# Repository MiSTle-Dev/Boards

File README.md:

The MiSTle projects can be used with off-the-shelf components and
some breadboard setup.

To simplify this the MiSTeryNano project provides additional custom designed hardware boards.

These boards are typically to be produced through a service like [JLCPCB](https://jlcpcb.com/). You might
want to check the [instructions in our wiki](https://github.com/MiSTle-Dev/.github/wiki/JLCPCB-Order).

## Shields and carrier boards

Shields are carrier boards that carry one or more off-the-shelf development boards, connect them and provide them with additional peripherals like USB Hubs, MIDI ports, Joystick ports etc.

  - The [MiSTeryShield20k](misteryshield20k) is a base board for
  the Tang Nano 20k and the M0S Dock with a DB9 joystick connector and
  MIDI ports
  - [MiSTeryShield20k RPiPico](misteryshield20k_rpipico) is a board similar to the
  [MiSTeryShield20k](misteryshield20k) but using a Raspberry Pi Pico instead of the M0S Dock and with a USB hub already built-in
  - The [MiSTeryShield20k lite](misteryshield20k_lite) is also a base
  board for the Tang Nano 20k. It includes the RP2040 and a USB-A
  port and is a minimal all-in-one solution for the Tang Nano 20k.
  - The [Icepi carrier](icepi_carrier) is a base board for the [Icepi-Zero](https://github.com/cheyao/icepi-zero) adds the FPGA Companion as well as USB and Joystick ports

## Complete stand-alone solutions

The stand-alone boards don't require any further daughter boards to be plugged in. They come with all the necessary parts
including the Companion, the FPGA and a set of useful peripherals already integrated into one single board. These boards are
also meant to be used as a basis for further designs using a modified set of peripherals or meant to fit certain cases.

  - The [MiSTeryDev20k](misterydev20k) was the first complete all-in-one MiSTle board. It's based on the the GW2AR-LV18 FPGA
  (the same one as on the Tang Nano 20k) and is fully compatible with any core developed for the Tang nano 20k.
  - The [MiSTle GW3A-LV20 Dev](mistle_gw3a_20) is derived from the [MiSTeryDev20k](misterydev20k) and replaces the GW2AR-LV18 FPGA
  with the GW3A-LV20 which is slightly newer and has a little more capacity than the GW2AR-LV18.

## MCU PMOD's

Many FPGA boards provide so-called PMOD ports. These can be used to add the FPGA Companion MCU to those boards. The
MCU PMOD's provide a PMOD connector to common MCU developments boards and makes them compatible with typical FPGA PMOD ports.

FPGA boards providing PMOD ports include the Tang Primer 20K, Primer 25K, Mega 60k/138K NEO, Mega138kPro and Console 60k/138k

  - The [PMOD M0S](m0s_pmod) provides a PMOD port for the M0S Dock (BL616 µC)
  - The [PMOD PiPico](pipico_pmod) provides a PMOD port for Raspberry Pi Pico and (W)ifi
  - The [PMOD PiZero](pizero_pmod) provides a PMOD port for Raspberry Pi Pico compatible RP2040-ZERO board

## Other boards

  - The [Console Hub](console_hub) is a small 4 port USB Hub designed to be used with the Tang Console allowing it to be powered via USB-C through the Hub.
  - The [T20 PMOD](t20_pmod) is an add-on for the Efinix T20BGA256 development board adding a PMOD for HDMI usage, the SD card slot and a Raspberry Pi PICO incl. USB-A header to it making it a complete MiSTeryNano setup.
  - The [LVDS2TMDS board](lvds2tmds) is and add-on for the Efinix T20BGA256 development board converting its LVDS outputs to TMDS allowing to drive regular digital video signals
  - The [Atari ST Keyboard](atarist_keyboard) design is a tiny 50% Atari ST style keyboard which is meant to become the basis for a Mini Atari ST
  - [MisteryShield20k DS2 Adapter](misteryshield20k_ds2_adapter) is an add-on for the [MiSTeryShield20k](misteryshield20k) allowing to connect Playstation Dualshock 2 Game controllers to it

## Related projects

Further hardware is available in related projects:

  - [MisteryNano Case](https://github.com/prcoder-1/MiSTeryNano-Case) is a 3d printable case design for the bare Tang Nano 20k (no shields) with room and mounting instructions for expansion connectors and an optional M0S Dock
  - [Nano-Hub](https://github.com/Mangerrione/Nano-Hub), a Tang Nano 20k sized USB Hub
  - [Nano-Box](https://github.com/Mangerrione/Nano-Box), a Amiga themed case for the NanoMig

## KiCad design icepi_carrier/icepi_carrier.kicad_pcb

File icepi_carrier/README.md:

# MiSTle Icepi Carrier

This is a carrier/base board for the [Icepi-Zero](https://github.com/cheyao/icepi-zero).
It adds the FPGA Companion with its USB ports and two classic Dsub9 joystick ports.

The IcePi mounts face down onto the carrier which will then provide the IcePi with an
[RP2350 as FPGA Companion](https://github.com/MiSTle-Dev/FPGA-Companion), two DB9
joystick/mouse ports and a few LEDs.

> [!WARNING]
> The IcePi Zero needs to be mounted face down. Otherwise the IcePi and/or the carrier
> board may be damaged!

This carrier board is supported by the [Lattice/IcePi port of NanoMig](https://github.com/MiSTle-Dev/NanoMig/tree/main/src/lattice/icepi-zero). 

> [!IMPORTANT]
> The 3.3V voltage regulation of the IcePi is being used for the carrier as well. This means
> that the RP2350 on the carrier will not work without the IcePi installed.

The RP2350 on the IcePi Carrier runs the [PICO2 variant of the FPGA Companion firmware](https://github.com/MiSTle-Dev/FPGA-Companion/tree/main/src/rp2040) which is configured like so:

```
$ cd FPGA-Companion/src/rp2040
$ mkdir build
$ cd build
$ cmake -DBOARD=PICO2 ..
...
$ make
```

The resulting ```fpga_companion.uf2``` can be copied via USB to the Carrier.

See the [schematics](icepi_carrier_sch.pdf) and the [board layout](icepi_carrier_pcb.pdf).

## Production

This board can be manfactured through [JLCPCBs assembly service](http://jlcpcb.com) using the [production data](production). The production data does not include the pin header/socket required to mount the IcePi as this needs to match what's mounted on the IcePi itself.

## History

  - V1.0: Initial version
  - V1.0a: Replaced ws2812b with slightly bigger one with better availability at JLC

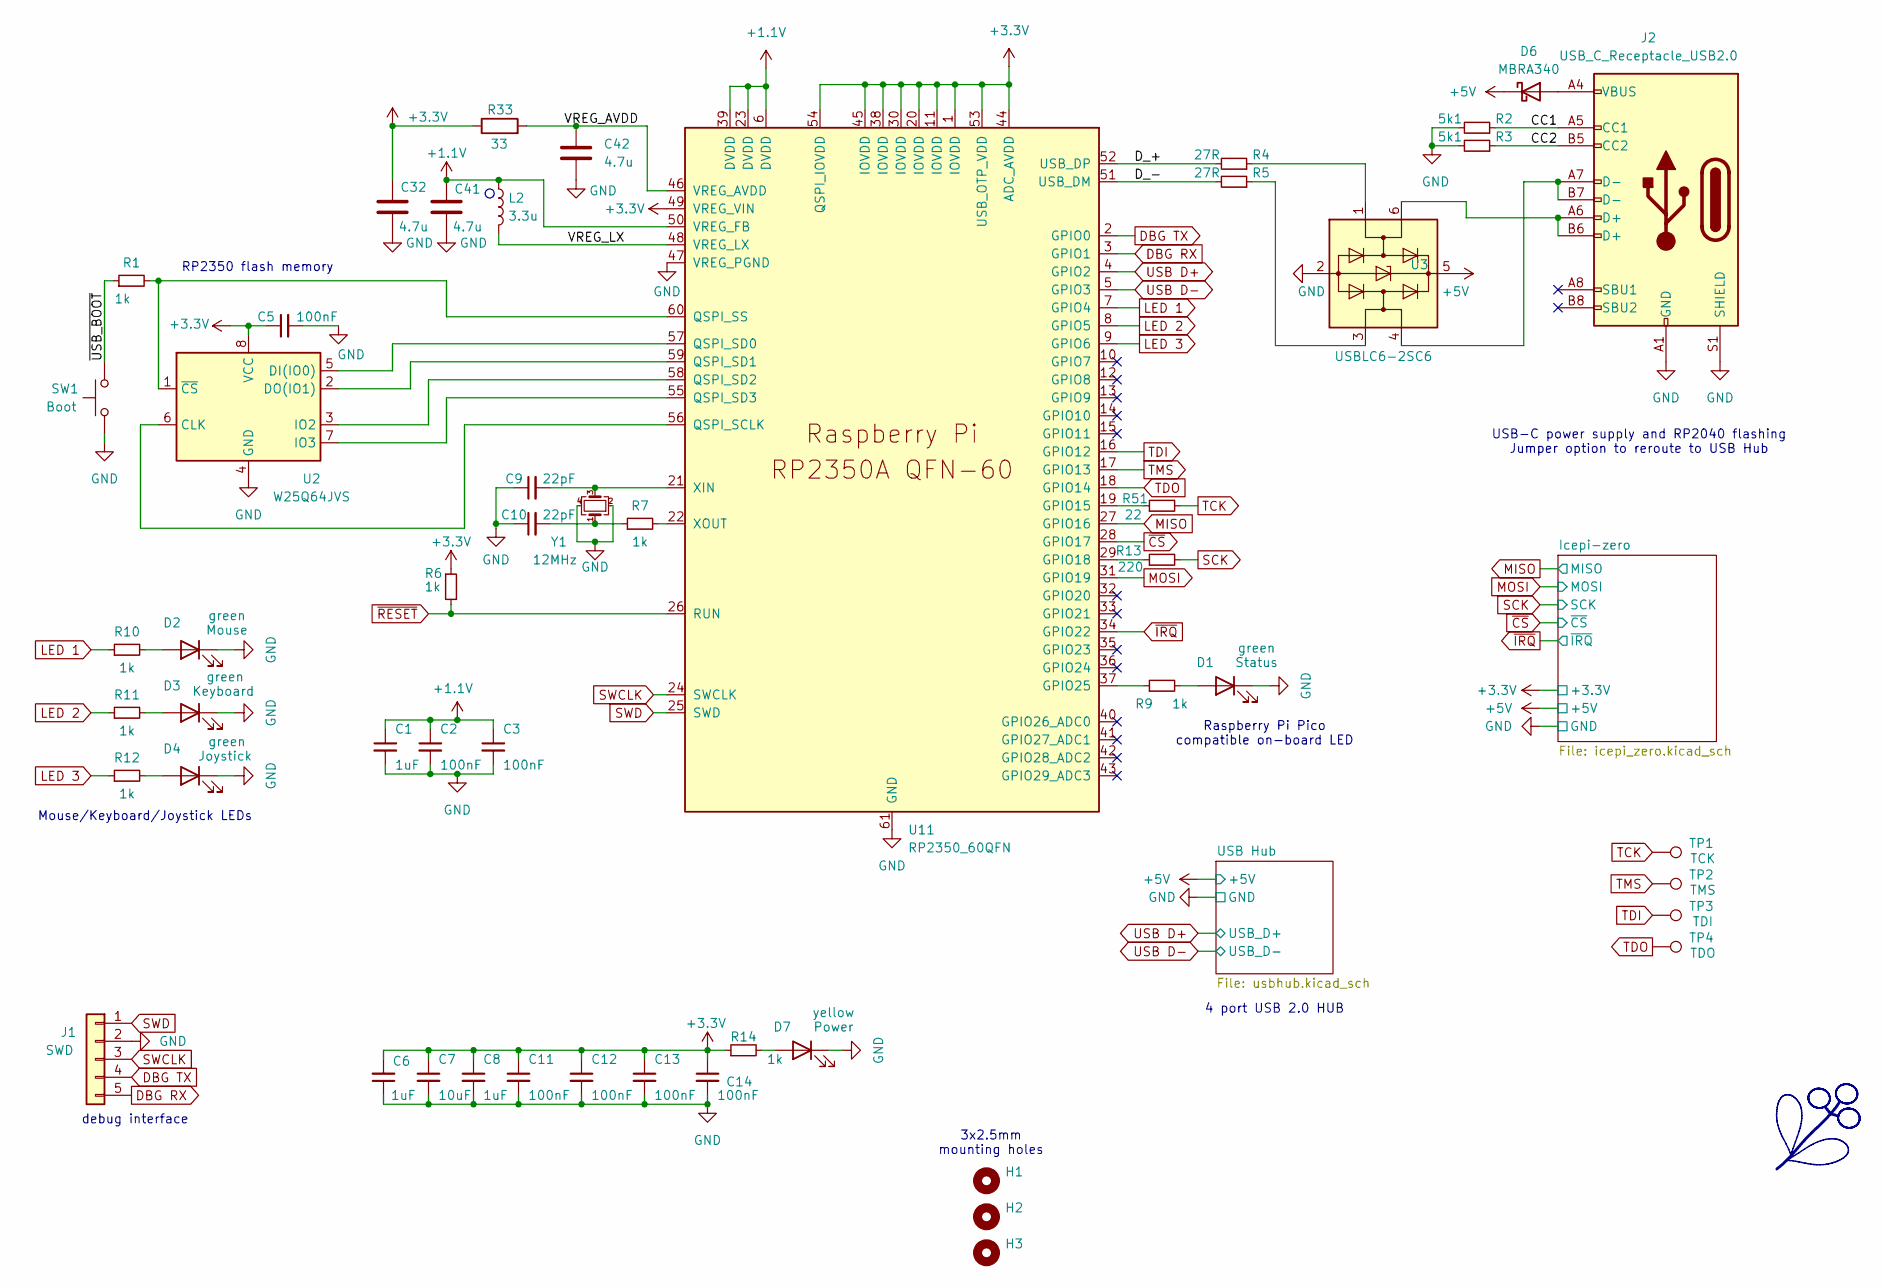
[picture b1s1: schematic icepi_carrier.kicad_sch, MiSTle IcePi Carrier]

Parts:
C1, C6, C8: 1uF; C_0402_1005Metric; LCSC Part # C52923
C2, C3, C5, C11, C12, C13, C14: 100nF; C_0402_1005Metric; LCSC Part # C1525
C7: 10uF; C_0402_1005Metric; LCSC Part # C15525
C9, C10: 22pF; C_0402_1005Metric; LCSC Part # C1555
C32, C41, C42: 4.7u; C_0402_1005Metric; LCSC Part # C23733
D1, D2, D3, D4: green; LED_0805_2012Metric; LCSC Part # C2297
D6: MBRA340; D_SMA; LCSC Part # C8678
D7: yellow; LED_0805_2012Metric; LCSC Part # C2296
H1, H2, H3: MountingHole; MountingHole_2.7mm_M2.5
J1: SWD; PinHeader_1x05_P2.54mm_Horizontal; LCSC Part # C492404
J2: USB_C_Receptacle_USB2.0; USB_C_Receptacle_HRO_TYPE-C-31-M-12; LCSC Part # C165948
L2: 3.3u; L_Changjiang_FTC201610D; LCSC Part # C42411119
R1, R6, R7, R9, R10, R11, R12, R14: 1k; R_0402_1005Metric; LCSC Part # C11702
R2, R3: 5k1; R_0402_1005Metric; LCSC Part # C25905
R4, R5: 27R; R_0603_1608Metric; LCSC Part # C25190
R13: 220; R_0402_1005Metric; LCSC Part # C25091
R33: 33; R_0402_1005Metric; LCSC Part # C25105
R51: 22; R_0402_1005Metric; LCSC Part # C25092
SW1: Boot; SW_SPST_TL3342; LCSC Part # C318884
TP1, TP2, TP3, TP4: TestPoint; TestPoint_Pad_D1.0mm
U2: W25Q64JVS; SOIC-8_5.3x5.3mm_P1.27mm; LCSC Part # C179171
U3: USBLC6-2SC6; SOT-23-6; LCSC Part # C2827654
U11: RP2350_60QFN; RP2350-QFN-60-1EP_7x7_P0.4mm_EP3.4x3.4mm_ThermalVias; LCSC Part # C42411118
Y1: 12MHz; Crystal_SMD_3225-4Pin_3.2x2.5mm; LCSC Part # C20625731

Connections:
+1.1V: C1.1, C2.1, C3.1, C41.1, L2.1, U11.6 (DVDD), U11.23 (DVDD), U11.39 (DVDD), U11.50 (VREG_FB)
+3.3V: C5.1, C6.2, C7.1, C8.1, C11.1, C12.1, C13.1, C14.1, C32.1, R6.1, R14.1, R33.1, U2.8 (VCC), U11.1 (IOVDD), U11.11 (IOVDD), U11.20 (IOVDD), U11.30 (IOVDD), U11.38 (IOVDD), U11.44 (ADC_AVDD), U11.45 (IOVDD), U11.49 (VREG_VIN), U11.53 (USB_OTP_VDD), U11.54 (QSPI_IOVDD); also elsewhere on the board
+5V: D6.1 (K), U3.5 (VBUS); also elsewhere on the board
/CC1: J2.A5 (CC1), R2.1
/CC2: J2.B5 (CC2), R3.1
/D_+: R4.2, U11.52 (USB_DP)
/D_-: R5.2, U11.51 (USB_DM)
/VREG_AVDD: C42.1, R33.2, U11.46 (VREG_AVDD)
/VREG_LX: L2.2, U11.48 (VREG_LX)
/~USB_BOOT: R1.1, SW1.2
DBG RX: J1.5, U11.3 (GPIO1)
DBG TX: J1.4, U11.2 (GPIO0)
GND: C1.2, C2.2, C3.2, C5.2, C6.1, C7.2, C8.2, C9.1, C10.1, C11.2, C12.2, C13.2, C14.2, C32.2, C41.2, C42.2, D1.1 (K), D2.1 (K), D3.1 (K), D4.1 (K), D7.1 (K), J1.2, J2.A1 (GND), J2.A12 (GND), J2.B1 (GND), J2.B12 (GND), J2.S1 (SHIELD), R2.2, R3.2, SW1.1, U2.4 (GND), U3.2 (GND), U11.47 (VREG_PGND), U11.61 (GND), Y1.2, Y1.4; also elsewhere on the board
LED 1: R10.1, U11.7 (GPIO4)
LED 2: R11.1, U11.8 (GPIO5)
LED 3: R12.1, U11.9 (GPIO6)
MISO: U11.27 (GPIO16); also elsewhere on the board
MOSI: U11.31 (GPIO19); also elsewhere on the board
unnamed: C10.2, R7.1, Y1.1
unnamed: D1.2 (A), R9.2
unnamed: D2.2 (A), R10.2
unnamed: D3.2 (A), R11.2
unnamed: D4.2 (A), R12.2
unnamed: D6.2 (A), J2.A4 (VBUS), J2.A9 (VBUS), J2.B4 (VBUS), J2.B9 (VBUS)
unnamed: D7.2 (A), R14.2
unnamed: J2.A6 (D+), J2.B6 (D+), U3.6 (I/O1)
unnamed: J2.A7 (D-), J2.B7 (D-), U3.4 (I/O2)
unnamed: R4.1, U3.1 (I/O1)
unnamed: R5.1, U3.3 (I/O2)
unnamed: R51.1, U11.19 (GPIO15)
unnamed: R13.1, U11.29 (GPIO18)
unnamed: R9.1, U11.37 (GPIO25)
unnamed: U2.6 (CLK), U11.56 (QSPI_SCLK)
unnamed: U2.5 (DI(IO0)), U11.57 (QSPI_SD0)
unnamed: U2.2 (DO(IO1)), U11.59 (QSPI_SD1)
unnamed: U2.3 (IO2), U11.58 (QSPI_SD2)
unnamed: U2.7 (IO3), U11.55 (QSPI_SD3)
unnamed: R1.2, U2.1 (~CS), U11.60 (QSPI_SS)
unnamed: C9.2, U11.21 (XIN), Y1.3
unnamed: R7.2, U11.22 (XOUT)
SCK: R13.2; also elsewhere on the board
SWCLK: J1.3, U11.24 (SWCLK)
SWD: J1.1, U11.25 (SWD)
TCK: R51.2, TP1.1 (1_1)
TDI: TP3.1 (1_1), U11.16 (GPIO12)
TDO: TP4.1 (1_1), U11.18 (GPIO14)
TMS: TP2.1 (1_1), U11.17 (GPIO13)
USB D+: U11.4 (GPIO2); also elsewhere on the board
USB D-: U11.5 (GPIO3); also elsewhere on the board
~CS: U11.28 (GPIO17); also elsewhere on the board
~IRQ: U11.34 (GPIO22); also elsewhere on the board
~RESET: R6.2, U11.26 (RUN)

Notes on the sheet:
Mouse/Keyboard/Joystick LEDs
RP2350 flash memory
3x2.5mm mounting holes
4 port USB 2.0 HUB
debug interface
Raspberry Pi Pico compatible on-board LED
USB-C power supply and RP2040 flashing Jumper option to reroute to USB Hub

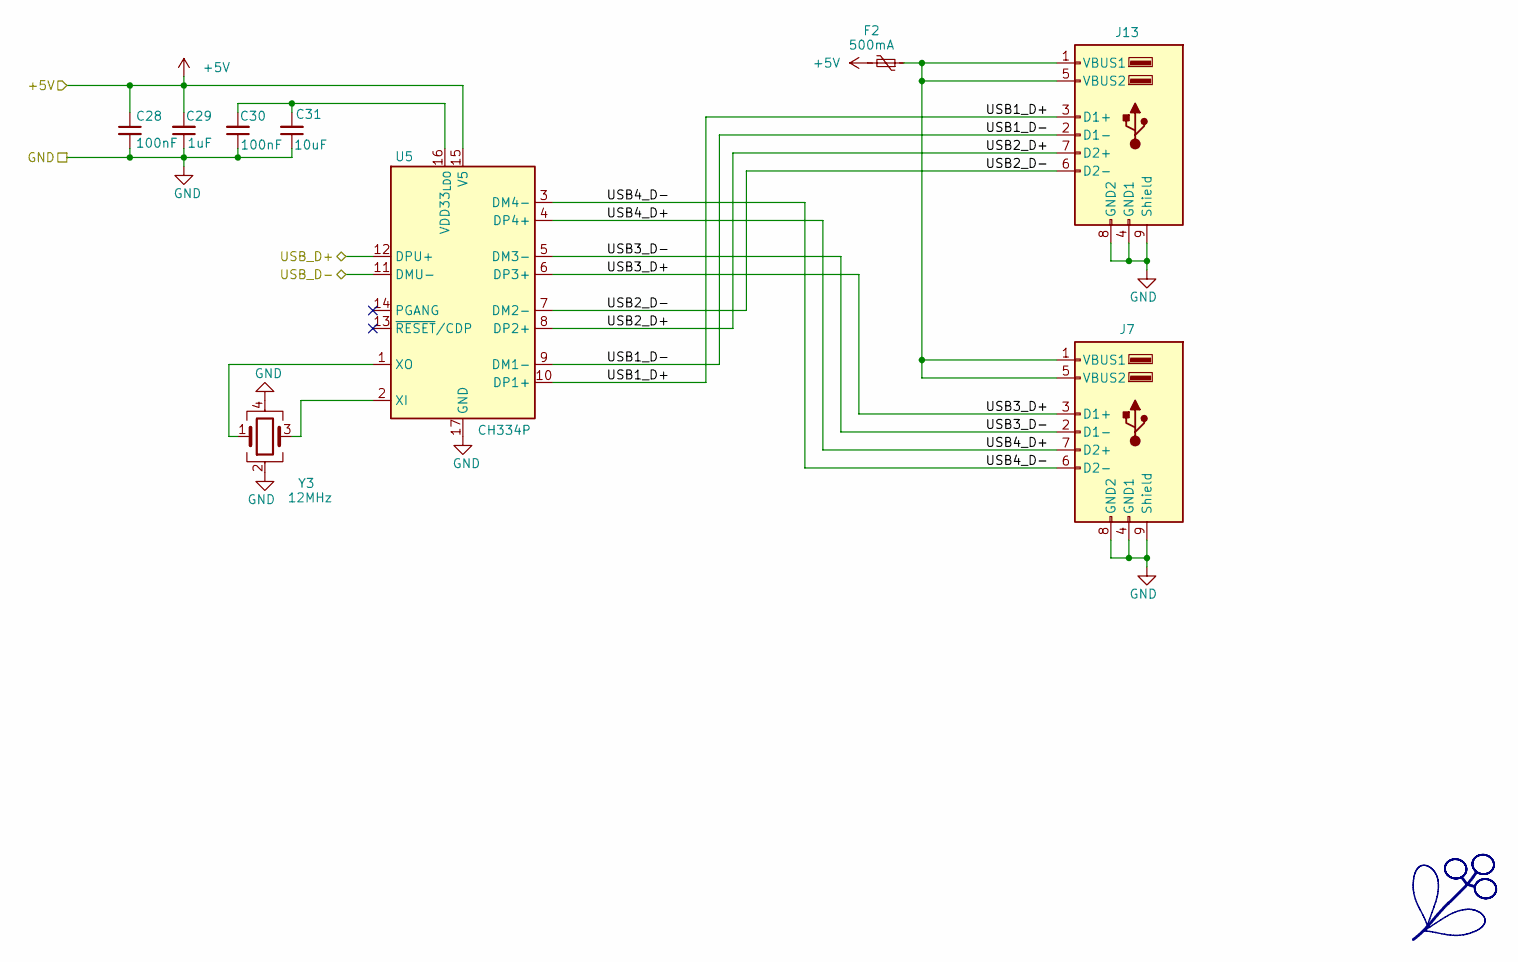
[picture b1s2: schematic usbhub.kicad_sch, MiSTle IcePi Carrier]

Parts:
C28, C30: 100nF; C_0402_1005Metric; LCSC Part # C1525
C29: 1uF; C_0402_1005Metric; LCSC Part # C52923
C31: 10uF; C_0402_1005Metric; LCSC Part # C15525
F2: 500mA; Fuse_1206_3216Metric; LCSC Part # C70076
J7, J13: USB_A_Stacked; USB_A_Wuerth_61400826021_Horizontal_Stacked; LCSC Part # C456021
U5: CH334P; QFN-16-1EP_3x3mm_P0.5mm_EP1.45x1.45mm_ThermalVias; LCSC Part # C5373042
Y3: 12MHz; Crystal_SMD_3225-4Pin_3.2x2.5mm; LCSC Part # C9002

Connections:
+5V: C28.1, C29.2, F2.2, U5.15 (V5); also elsewhere on the board
/USB Hub/USB1_D+: J13.3 (D1+), U5.10 (DP1+)
/USB Hub/USB1_D-: J13.2 (D1-), U5.9 (DM1-)
/USB Hub/USB2_D+: J13.7 (D2+), U5.8 (DP2+)
/USB Hub/USB2_D-: J13.6 (D2-), U5.7 (DM2-)
/USB Hub/USB3_D+: J7.3 (D1+), U5.6 (DP3+)
/USB Hub/USB3_D-: J7.2 (D1-), U5.5 (DM3-)
/USB Hub/USB4_D+: J7.7 (D2+), U5.4 (DP4+)
/USB Hub/USB4_D-: J7.6 (D2-), U5.3 (DM4-)
GND: C28.2, C29.1, C30.1, C31.1, J7.4 (GND1), J7.8 (GND2), J7.9 (Shield), J13.4 (GND1), J13.8 (GND2), J13.9 (Shield), U5.17 (GND), Y3.2, Y3.4; also elsewhere on the board
unnamed: F2.1, J7.1 (VBUS1), J7.5 (VBUS2), J13.1 (VBUS1), J13.5 (VBUS2)
unnamed: C30.2, C31.2, U5.16 (VDD33_{LDO})
unnamed: U5.2 (XI), Y3.3
unnamed: U5.1 (XO), Y3.1
USB D+: U5.12 (DPU+); also elsewhere on the board
USB D-: U5.11 (DMU-); also elsewhere on the board

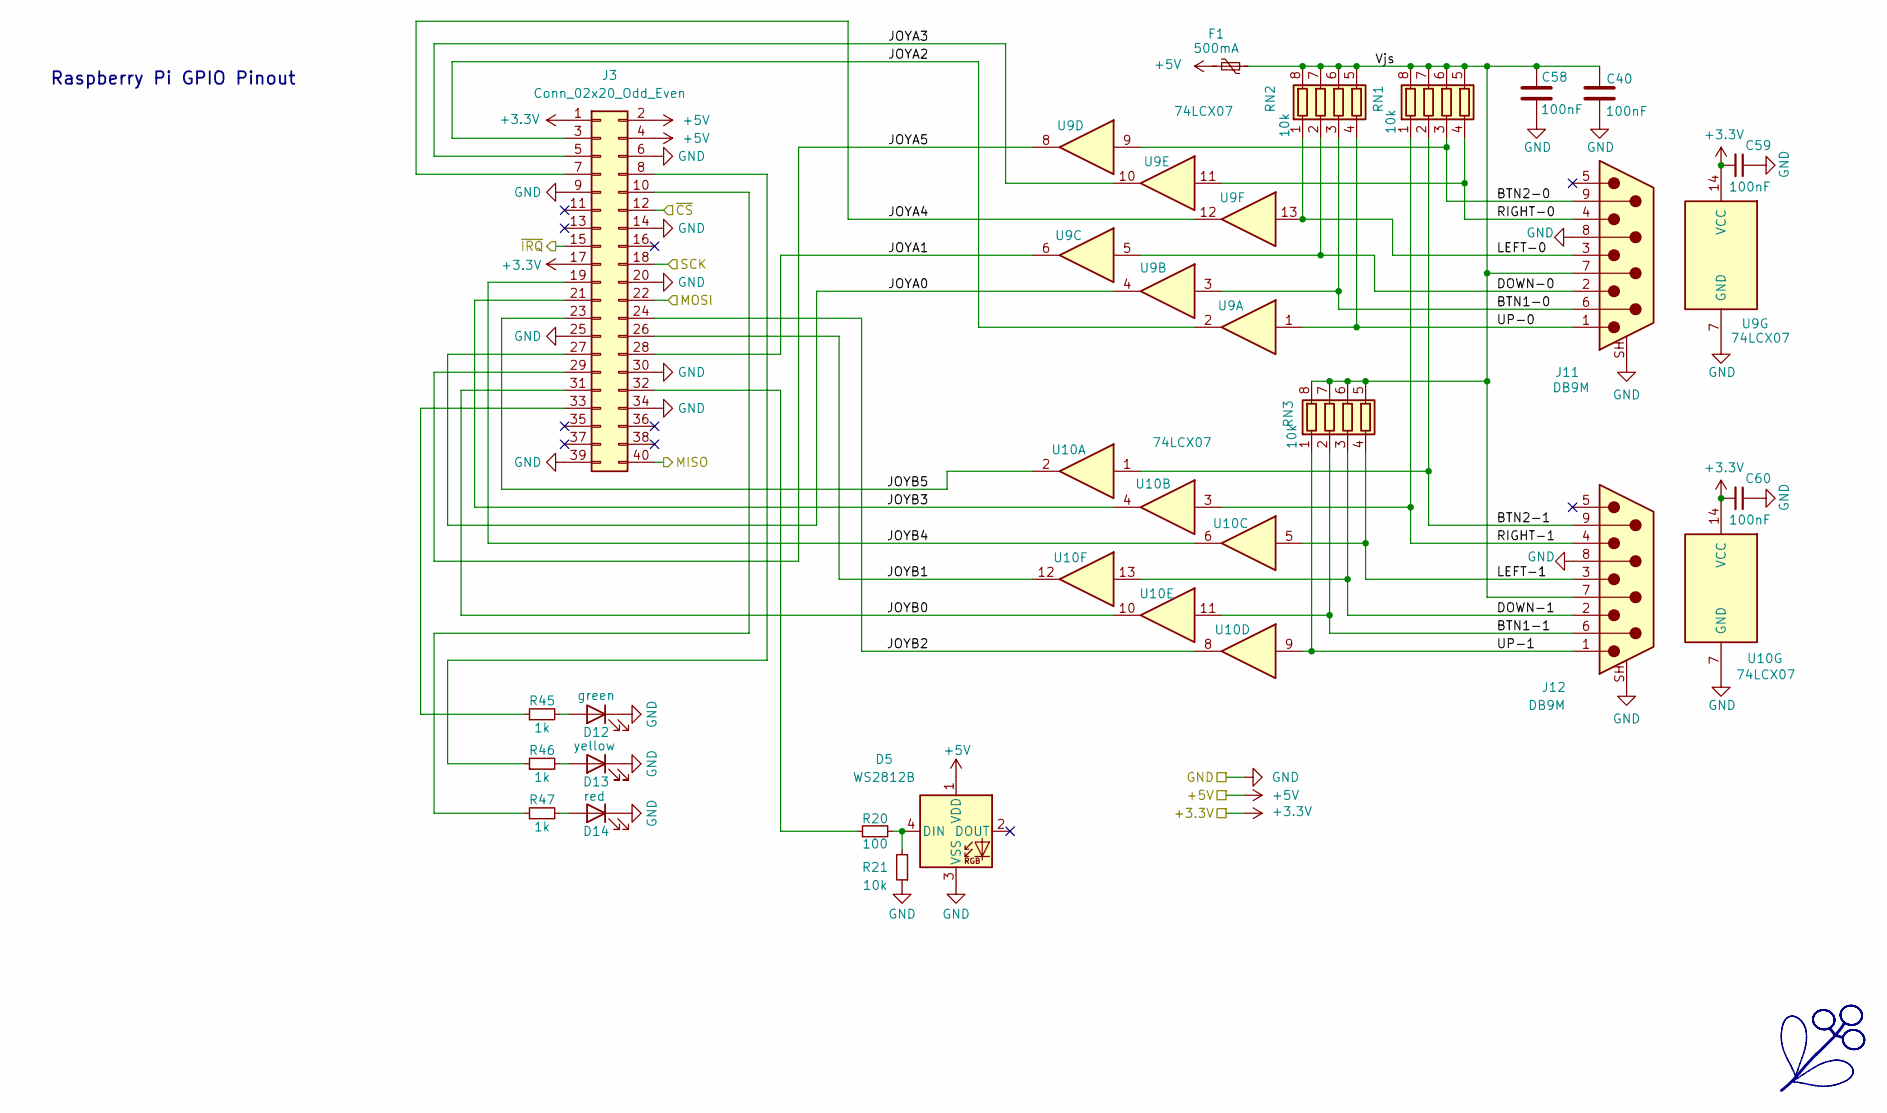
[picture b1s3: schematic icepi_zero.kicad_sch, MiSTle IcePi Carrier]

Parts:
C40, C58, C59, C60: 100nF; C_0402_1005Metric; LCSC Part # C1525
D5: WS2812B; LED_WS2812B-Mini_PLCC4_3.5x3.5mm; LCSC Part # C527089
D12: green; LED_0805_2012Metric; LCSC Part # C2297
D13: yellow; LED_0805_2012Metric; LCSC Part # C2296
D14: red; LED_0805_2012Metric; LCSC Part # C2295
F1: 500mA; Fuse_1206_3216Metric; LCSC Part # C70076
J3: Conn_02x20_Odd_Even; PinSocket_2x20_P2.54mm_Vertical
J11, J12: DB9M; DSUB-9_Pins_Horizontal_P2.77x2.84mm_EdgePinOffset7.70mm_Hou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; LCSC Part # C141880
R20: 100; R_0402_1005Metric; LCSC Part # C25076
R21: 10k; R_0402_1005Metric; LCSC Part # C25744
R45, R46, R47: 1k; R_0402_1005Metric; LCSC Part # C11702
RN1, RN2, RN3: 10k; R_Array_Concave_4x0603; LCSC Part # C110924
U9, U10: 74LCX07; TSSOP-14_4.4x5mm_P0.65mm; LCSC Part # C2676034

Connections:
+3.3V: C59.2, C60.2, J3.1, J3.17, U9.14 (VCC), U10.14 (VCC); also elsewhere on the board
+5V: D5.1 (VDD), F1.2, J3.2, J3.4; also elsewhere on the board
/Icepi-zero/BTN1-0: J11.6, RN2.3 (R3.1), U9.3
/Icepi-zero/BTN1-1: J12.6, RN3.2 (R2.1), U10.11
/Icepi-zero/BTN2-0: J11.9, RN1.3 (R3.1), U9.9
/Icepi-zero/BTN2-1: J12.9, RN1.2 (R2.1), U10.1
/Icepi-zero/DOWN-0: J11.2, RN2.2 (R2.1), U9.5
/Icepi-zero/DOWN-1: J12.2, RN3.3 (R3.1), U10.13
/Icepi-zero/JOYA0: J3.27, U9.4
/Icepi-zero/JOYA1: J3.28, U9.6
/Icepi-zero/JOYA2: J3.3, U9.2
/Icepi-zero/JOYA3: J3.5, U9.10
/Icepi-zero/JOYA4: J3.7, U9.12
/Icepi-zero/JOYA5: J3.29, U9.8
/Icepi-zero/JOYB0: J3.31, U10.10
/Icepi-zero/JOYB1: J3.26, U10.12
/Icepi-zero/JOYB2: J3.24, U10.8
/Icepi-zero/JOYB3: J3.21, U10.4
/Icepi-zero/JOYB4: J3.19, U10.6
/Icepi-zero/JOYB5: J3.23, U10.2
/Icepi-zero/LEFT-0: J11.3, RN2.1 (R1.1), U9.13
/Icepi-zero/LEFT-1: J12.3, RN3.4 (R4.1), U10.5
/Icepi-zero/RIGHT-0: J11.4, RN1.4 (R4.1), U9.11
/Icepi-zero/RIGHT-1: J12.4, RN1.1 (R1.1), U10.3
/Icepi-zero/UP-0: J11.1, RN2.4 (R4.1), U9.1
/Icepi-zero/UP-1: J12.1, RN3.1 (R1.1), U10.9
/Icepi-zero/Vjs: C40.2, C58.2, F1.1, J11.7, J12.7, RN1.5 (R4.2), RN1.6 (R3.2), RN1.7 (R2.2), RN1.8 (R1.2), RN2.5 (R4.2), RN2.6 (R3.2), RN2.7 (R2.2), RN2.8 (R1.2), RN3.5 (R4.2), RN3.6 (R3.2), RN3.7 (R2.2), RN3.8 (R1.2)
GND: C40.1, C58.1, C59.1, C60.1, D5.3 (VSS), D12.1 (K), D13.1 (K), D14.1 (K), J3.6, J3.9, J3.14, J3.20, J3.25, J3.30, J3.34, J3.39, J11.8, J11.SH (PAD), J12.8, J12.SH (PAD), R21.1, U9.7 (GND), U10.7 (GND); also elsewhere on the board
MISO: J3.40; also elsewhere on the board
MOSI: J3.22; also elsewhere on the board
unnamed: D5.4 (DIN), R20.2, R21.2
unnamed: D12.2 (A), R45.2
unnamed: D13.2 (A), R46.2
unnamed: D14.2 (A), R47.2
unnamed: J3.8, R46.1
unnamed: J3.10, R47.1
unnamed: J3.32, R20.1
unnamed: J3.33, R45.1
SCK: J3.18; also elsewhere on the board
~CS: J3.12; also elsewhere on the board
~IRQ: J3.15; also elsewhere on the board

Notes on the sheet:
Raspberry Pi GPIO Pinout

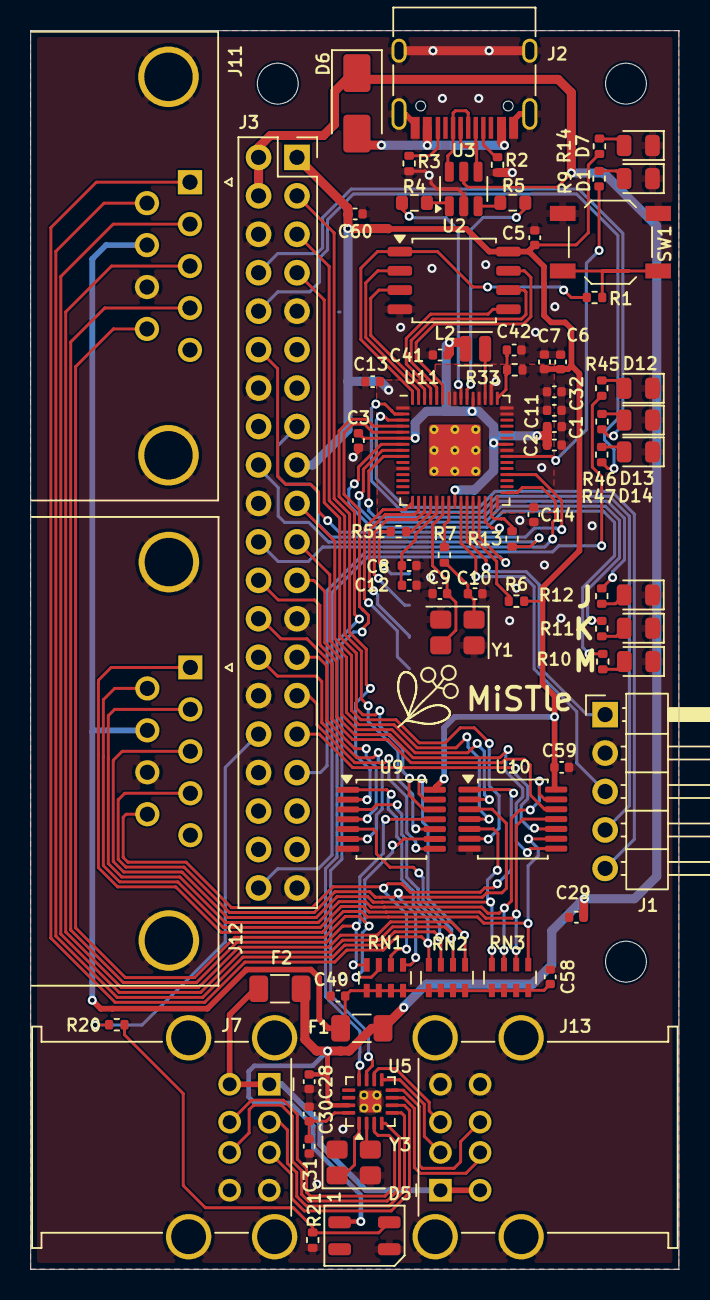
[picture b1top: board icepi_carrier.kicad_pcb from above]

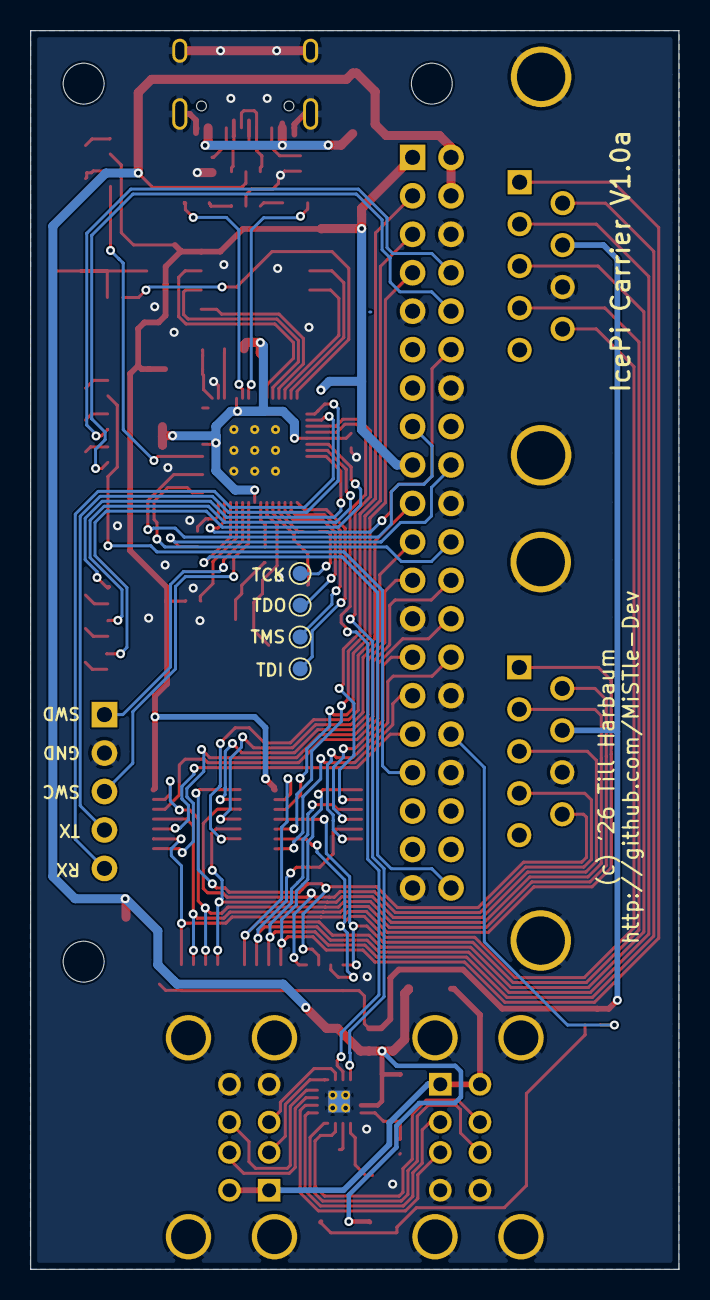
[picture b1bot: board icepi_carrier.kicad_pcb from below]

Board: 2 copper layers, 42.8 x 81.8 mm, 83 parts (4 on the bottom side), 97 nets.

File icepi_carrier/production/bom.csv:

Designator,Footprint,Quantity,Value,LCSC Part #
"C1, C29, C6, C8",0402,4,1uF,C52923
"C10, C9",0402,2,22pF,C1555
"C11, C12, C13, C14, C2, C28, C3, C30, C40, C5, C58, C59, C60",0402,13,100nF,C1525
"C31, C7",0402,2,10uF,C15525
"C32, C41, C42",0402,3,4.7u,C23733
"D1, D12, D2, D3, D4",0805,5,green,C2297
"D13, D7",0805,2,yellow,C2296
D14,0805,1,red,C2295
D5,LED_WS2812B-Mini_PLCC4_3.5x3.5mm,1,WS2812B,C527089
D6,D_SMA,1,MBRA340,C8678
"F1, F2",1206,2,500mA,C70076
J1,PinHeader_1x05_P2.54mm_Horizontal,1,SWD,C492404
"J11, J12",DSUB-9_Pins_Horizontal_P2.77x2.84mm_EdgePinOffset7.70mm_Housed_MountingHolesOffset9.12mm,2,DB9M,C141880
"J13, J7",USB_A_Wuerth_61400826021_Horizontal_Stacked,2,USB_A_Stacked,C456021
J2,USB_C_Receptacle_HRO_TYPE-C-31-M-12,1,USB_C_Receptacle_USB2.0,C165948
L2,L_Changjiang_FTC201610D,1,3.3u,C42411119
"R1, R10, R11, R12, R14, R45, R46, R47, R6, R7, R9",0402,11,1k,C11702
R13,0402,1,220,C25091
"R2, R3",0402,2,5k1,C25905
R20,0402,1,100,C25076
R21,0402,1,10k,C25744
R33,0402,1,33,C25105
"R4, R5",0603,2,27R,C25190
R51,0402,1,22,C25092
"RN1, RN2, RN3",R_Array_Concave_4x0603,3,10k,C110924
SW1,SW_SPST_TL3342,1,Boot,C318884
"U10, U9",TSSOP-14_4.4x5mm_P0.65mm,2,74LCX07,C2676034
U11,RP2350-QFN-60-1EP_7x7_P0.4mm_EP3.4x3.4mm_ThermalVias,1,RP2350_60QFN,C42411118
U2,SOIC-8_5.3x5.3mm_P1.27mm,1,W25Q64JVS,C179171
U3,SOT-23-6,1,USBLC6-2SC6,C2827654
U5,QFN-16-1EP_3x3mm_P0.5mm_EP1.45x1.45mm_ThermalVias,1,CH334P,C5373042
Y1,Crystal_SMD_3225-4Pin_3.2x2.5mm,1,12MHz,C20625731
Y3,Crystal_SMD_3225-4Pin_3.2x2.5mm,1,12MHz,C9002

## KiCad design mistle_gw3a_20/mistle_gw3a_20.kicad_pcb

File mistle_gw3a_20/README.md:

# GW3A-LV20/GW5A-LV25 DEV25K MiSTle development board

This board is derived from the [MiSTeryDev20k
board](https://github.com/MiSTle-Dev/Boards/tree/main/misterydev20k)
which was the first full custom board designed for the MiSTle project.

This board is a development board initially designed to test the
upcoming [GW3A-LV20 FPGA](https://www.gowinsemi.com/en/product/detail/84/) with the MiSTle
retro computing cores. It can also be used with the existing GW5A-LV25
FPGA as seen in the image above.

The NanoMig and C64Nano had [been
prepared to run on the GW3A](https://github.com/MiSTle-Dev/NanoMig/tree/main/src/mistle/gw3a_20)
to ensure that the cores can be synthesized and especially to verify
the pin mapping. Depiced above is the board with the GW5A-25K mounted and running
the [GW5A-LV25 variant](https://github.com/MiSTle-Dev/NanoMig/tree/main/src/mistle/gw5a_25)
of the [NanoMig FPGA Core](https://github.com/MiSTle-Dev/NanoMig).

## Goals
  - Get used to the new GW3A family of FPGAs
    - Update openFPGAloader
    - Verify use of external SDRAM
  - Update Companion to RP2350
    - Use additional PIO for JTAG

## Current state

  - Initial schematic and board derived from the [MiSTeryDev20k board](https://github.com/MiSTle-Dev/Boards/tree/main/misterydev20k)
  - [NanoMig](https://github.com/MiSTle-Dev/NanoMig) core [synthesized for GW3A-LV20](https://github.com/MiSTle-Dev/NanoMig/tree/main/src/mistle/gw3a_20) :heavy_check_mark:
    - LUT usage around 80%
  - Schematic updates
    - GW2AR-LV18 FPGA replaced by GW3A-LV20 :heavy_check_mark:
    - Updated pin mapping :heavy_check_mark:
    - Added external 256MBit (16M*16) SDRAM as the GW3A-LV20 has no internal SDRAM :heavy_check_mark: 
    - External peripherals mapped :heavy_check_mark:
    - Update FPGA Power Supply :heavy_check_mark:
    - Add smoothing capacitors and similar :heavy_check_mark:
    - Initial routing :heavy_check_mark:
    - Verify schematic :wrench:
       - Check updated SD card wiring :heavy_check_mark:
       - Check FPGA power supply :heavy_check_mark:
       - Update from rp2040 to rp2350 :heavy_check_mark:
       - Check compatibility with GW5A-LV25-LQ144 :heavy_check_mark:
    - Verify PCB :wrench:
    - Update JLCPCB part numbers :heavy_check_mark:
    - Generate [JLCPCB production data](production) :heavy_check_mark:
    - Order partially assembled boards :heavy_check_mark:
    - Order FPGAs :heavy_check_mark:	
    - Waiting for delivery :heavy_check_mark:	
    - Update Companion firmware for rp2350 :heavy_check_mark:	
    - Solder and test FPGA :heavy_check_mark:	
    - Solder and test SDRAM :heavy_check_mark:
    - Testing :heavy_check_mark:
    - Make use of bigger FPGA (AGA)

## FPGA Companion

The FPGA Companion needs to be built with

   ```cmake -DBOARD=DEV25K ..```

The Companion will then act as the regular support device during
runtime but will also provide USB/JTAG functionality for setup and
flashing from a PC.

## Cores

Currently the NanoMig and C64Nano had been ported to this board. A tested and
fully working core for the GW5A-25K is available and can be built using
the following command:

   ```build.sh mistle_gw5a_25```

The GW3A-20K NanoMig variant can also be built in similar way:

   ```build.sh mistle_gw3a_20```

This is untested for obvious reasons.

## Issues with V1.0

  - Polarity of ```MODE0``` os wrong and prevents FPGA flash boot/usage
  - Flash ```IO2``` and ```IO3``` should probably be FPGA pins ```MI2``` and ```MI3``` instead ```DO2``` and ```DO3```. This is not critical but probably prevents a QSPI FPGA boot. This is misleading in figure 4-4 of [UG1356-1.0E_GW3A series of FPGA Products Schematic Manual.pdf](https://www.gowinsemi.com/en/document/chkLogin/?forward=product%2C3373).

## Preliminary schematic

The schematic is a work in progress and can be viewed [here](https://github.com/MiSTle-Dev/Boards/blob/main/mistle_gw3a_20/mistle_gw3a_20_sch.pdf).

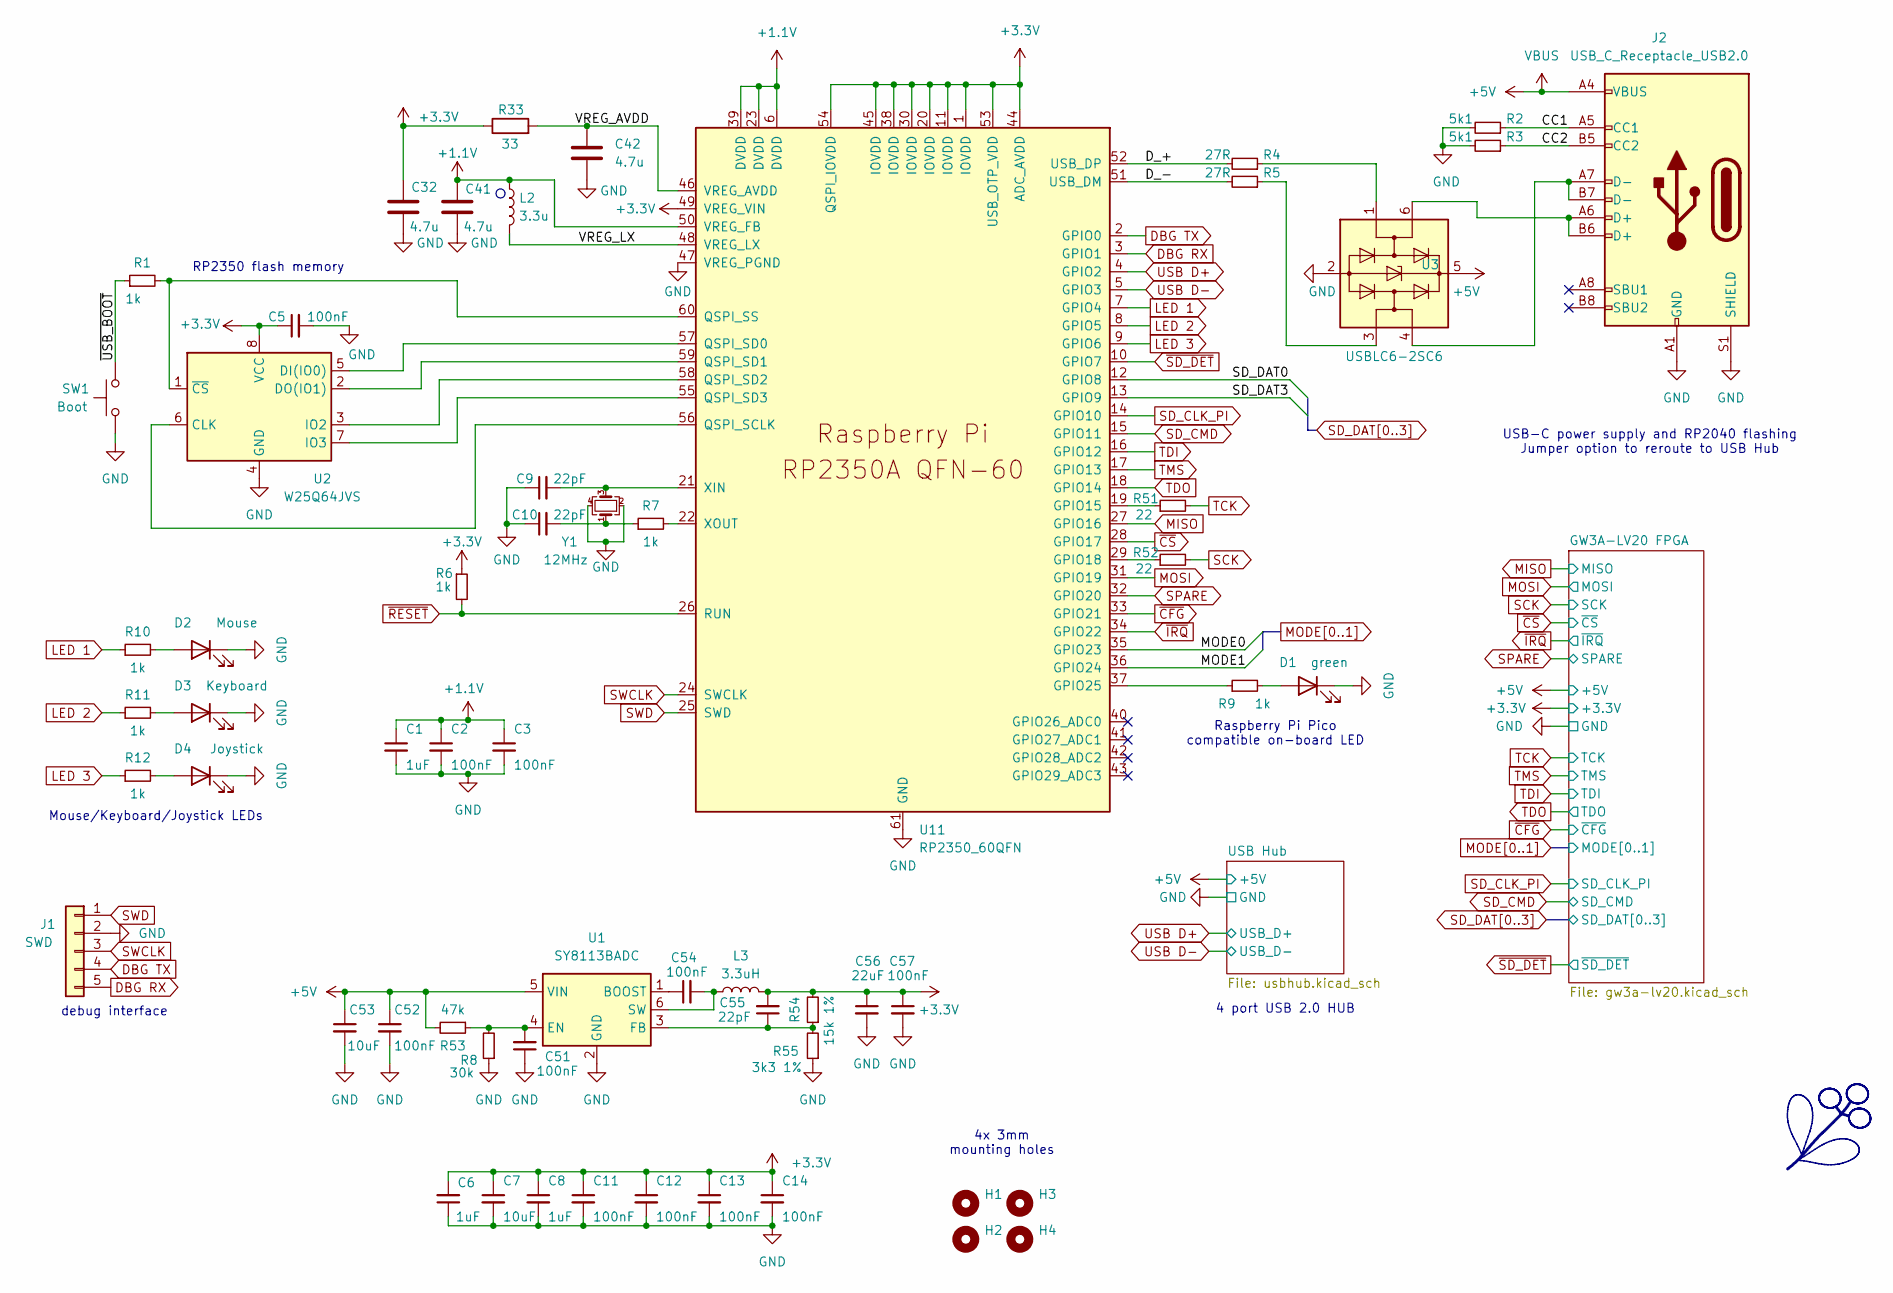
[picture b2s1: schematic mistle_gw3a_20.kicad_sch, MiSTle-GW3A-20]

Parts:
C1, C6, C8: 1uF; C_0402_1005Metric; LCSC Part # C52923
C2, C3, C5, C11, C12, C13, C14, C51, C54: 100nF; C_0402_1005Metric; LCSC Part # C1525
C7: 10uF; C_0402_1005Metric; LCSC Part # C15525
C9, C10, C55: 22pF; C_0402_1005Metric; LCSC Part # C1555
C32, C41, C42: 4.7u; C_0402_1005Metric; LCSC Part # C23733
C52, C57: 100nF; C_0603_1608Metric; LCSC Part # C14663
C53: 10uF; C_0603_1608Metric; LCSC Part # C19702
C56: 22uF; C_0603_1608Metric; LCSC Part # C84419
D1: green; LED_0805_2012Metric; LCSC Part # C2297
D2: Mouse; LED_0805_2012Metric; LCSC Part # C2297
D3: Keyboard; LED_0805_2012Metric; LCSC Part # C2297
D4: Joystick; LED_0805_2012Metric; LCSC Part # C2297
H1, H2, H3, H4: MountingHole; MountingHole_3.2mm_M3
J1: SWD; PinHeader_1x05_P2.54mm_Vertical; LCSC Part # C492404
J2: USB_C_Receptacle_USB2.0; USB_C_Receptacle_HRO_TYPE-C-31-M-12; LCSC Part # C165948
L2: 3.3u; L_Changjiang_FTC201610D; LCSC Part # C42411119
L3: 3.3uH; L_Sunlord_MWSA0402S; LCSC Part # C408336
R1, R6, R7, R9, R10, R11, R12: 1k; R_0402_1005Metric; LCSC Part # C11702
R2, R3: 5k1; R_0402_1005Metric; LCSC Part # C25905
R4, R5: 27R; R_0603_1608Metric; LCSC Part # C25190
R8: 30k; R_0402_1005Metric; LCSC Part # C138008
R33: 33; R_0402_1005Metric; LCSC Part # C25105
R51, R52: 22; R_0402_1005Metric; LCSC Part # C25092
R53: 47k; R_0402_1005Metric; LCSC Part # C25792
R54: 15k 1%; R_0402_1005Metric; LCSC Part # C25756
R55: 3k3 1%; R_0402_1005Metric; LCSC Part # C25890
SW1: Boot; SW_SPST_TL3342; LCSC Part # C318884
U1: SY8113BADC; TSOT-23-6; LCSC Part # C78989
U2: W25Q64JVS; SOIC-8_5.3x5.3mm_P1.27mm; LCSC Part # C179171
U3: USBLC6-2SC6; SOT-23-6; LCSC Part # C2827654
U11: RP2350_60QFN; RP2350-QFN-60-1EP_7x7_P0.4mm_EP3.4x3.4mm_ThermalVias; LCSC Part # C42411118
Y1: 12MHz; Crystal_SMD_3225-4Pin_3.2x2.5mm; LCSC Part # C20625731

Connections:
+1.1V: C1.1, C2.1, C3.1, C41.1, L2.1, U11.6 (DVDD), U11.23 (DVDD), U11.39 (DVDD), U11.50 (VREG_FB)
+3.3V: C5.1, C6.2, C7.1, C8.1, C11.1, C12.1, C13.1, C14.1, C32.1, C55.2, C56.1, C57.1, L3.2, R6.1, R33.1, R54.2, U2.8 (VCC), U11.1 (IOVDD), U11.11 (IOVDD), U11.20 (IOVDD), U11.30 (IOVDD), U11.38 (IOVDD), U11.44 (ADC_AVDD), U11.45 (IOVDD), U11.49 (VREG_VIN), U11.53 (USB_OTP_VDD), U11.54 (QSPI_IOVDD); also elsewhere on the board
+5V: C52.1, C53.1, J2.A4 (VBUS), J2.A9 (VBUS), J2.B4 (VBUS), J2.B9 (VBUS), R53.2, U1.5 (VIN), U3.5 (VBUS); also elsewhere on the board
/CC1: J2.A5 (CC1), R2.1
/CC2: J2.B5 (CC2), R3.1
/D_+: R4.2, U11.52 (USB_DP)
/D_-: R5.2, U11.51 (USB_DM)
/VREG_AVDD: C42.1, R33.2, U11.46 (VREG_AVDD)
/VREG_LX: L2.2, U11.48 (VREG_LX)
/~USB_BOOT: R1.1, SW1.2
DBG RX: J1.5, U11.3 (GPIO1)
DBG TX: J1.4, U11.2 (GPIO0)
GND: C1.2, C2.2, C3.2, C5.2, C6.1, C7.2, C8.2, C9.1, C10.1, C11.2, C12.2, C13.2, C14.2, C32.2, C41.2, C42.2, C51.1, C52.2, C53.2, C56.2, C57.2, D1.1 (K), D2.1 (K), D3.1 (K), D4.1 (K), J1.2, J2.A1 (GND), J2.A12 (GND), J2.B1 (GND), J2.B12 (GND), J2.S1 (SHIELD), R2.2, R3.2, R8.1, R55.1, SW1.1, U1.2 (GND), U2.4 (GND), U3.2 (GND), U11.47 (VREG_PGND), U11.61 (GND), Y1.2, Y1.4; also elsewhere on the board
LED 1: R10.1, U11.7 (GPIO4)
LED 2: R11.1, U11.8 (GPIO5)
LED 3: R12.1, U11.9 (GPIO6)
MISO: U11.27 (GPIO16); also elsewhere on the board
MODE0: U11.35 (GPIO23); also elsewhere on the board
MODE1: U11.36 (GPIO24); also elsewhere on the board
MOSI: U11.31 (GPIO19); also elsewhere on the board
unnamed: C10.2, R7.1, Y1.1
unnamed: D1.2 (A), R9.2
unnamed: D2.2 (A), R10.2
unnamed: D3.2 (A), R11.2
unnamed: D4.2 (A), R12.2
unnamed: J2.A6 (D+), J2.B6 (D+), U3.6 (I/O1)
unnamed: J2.A7 (D-), J2.B7 (D-), U3.4 (I/O2)
unnamed: R4.1, U3.1 (I/O1)
unnamed: R5.1, U3.3 (I/O2)
unnamed: C54.1, U1.1 (BOOST)
unnamed: C51.2, R8.2, R53.1, U1.4 (EN)
unnamed: C55.1, R54.1, R55.2, U1.3 (FB)
unnamed: C54.2, L3.1, U1.6 (SW)
unnamed: R51.1, U11.19 (GPIO15)
unnamed: R52.1, U11.29 (GPIO18)
unnamed: R9.1, U11.37 (GPIO25)
unnamed: U2.6 (CLK), U11.56 (QSPI_SCLK)
unnamed: U2.5 (DI(IO0)), U11.57 (QSPI_SD0)
unnamed: U2.2 (DO(IO1)), U11.59 (QSPI_SD1)
unnamed: U2.3 (IO2), U11.58 (QSPI_SD2)
unnamed: U2.7 (IO3), U11.55 (QSPI_SD3)
unnamed: R1.2, U2.1 (~CS), U11.60 (QSPI_SS)
unnamed: C9.2, U11.21 (XIN), Y1.3
unnamed: R7.2, U11.22 (XOUT)
SCK: R52.2; also elsewhere on the board
SD_CLK_PI: U11.14 (GPIO10); also elsewhere on the board
SD_CMD: U11.15 (GPIO11); also elsewhere on the board
SD_DAT0: U11.12 (GPIO8); also elsewhere on the board
SD_DAT3: U11.13 (GPIO9); also elsewhere on the board
SPARE: U11.32 (GPIO20); also elsewhere on the board
SWCLK: J1.3, U11.24 (SWCLK)
SWD: J1.1, U11.25 (SWD)
TCK: R51.2; also elsewhere on the board
TDI: U11.16 (GPIO12); also elsewhere on the board
TDO: U11.18 (GPIO14); also elsewhere on the board
TMS: U11.17 (GPIO13); also elsewhere on the board
USB D+: U11.4 (GPIO2); also elsewhere on the board
USB D-: U11.5 (GPIO3); also elsewhere on the board
~CFG: U11.33 (GPIO21); also elsewhere on the board
~CS: U11.28 (GPIO17); also elsewhere on the board
~IRQ: U11.34 (GPIO22); also elsewhere on the board
~RESET: R6.2, U11.26 (RUN)
~SD_DET: U11.10 (GPIO7); also elsewhere on the board

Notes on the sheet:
Mouse/Keyboard/Joystick LEDs
RP2350 flash memory
4x 3mm mounting holes
4 port USB 2.0 HUB
debug interface
Raspberry Pi Pico compatible on-board LED
USB-C power supply and RP2040 flashing Jumper option to reroute to USB Hub

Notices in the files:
lvds2tmds/lvds2tmds.kicad_pcb:
(c) 2025 Till Harbaum
misteryshield20k_rpipico_dual_db9/MiSTeryShield20kRPiPicoUSB_usbhub.kicad_sch:
Original Design (c) 2025 by Stefan Voss
